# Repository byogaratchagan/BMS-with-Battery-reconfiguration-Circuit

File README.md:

# 2ND Prototype design requiremetns

* Switch circuit
* Switch circuit MOSFET driver and control circuit
    * Planar Transformer design for Gate source Voltage source
* Controller and Display
* Enclosure Design

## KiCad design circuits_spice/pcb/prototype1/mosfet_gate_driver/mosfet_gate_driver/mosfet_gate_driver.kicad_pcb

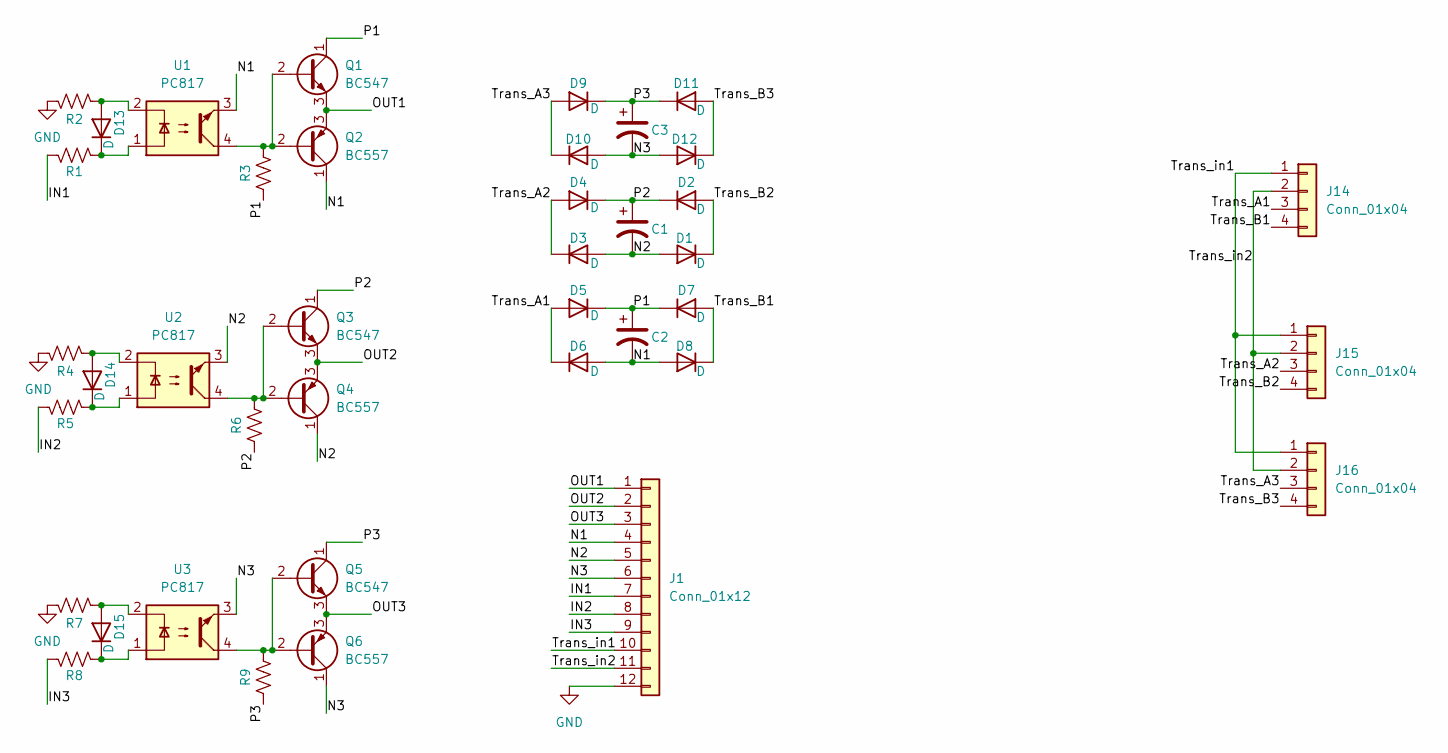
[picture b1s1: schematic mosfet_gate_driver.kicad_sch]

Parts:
C1, C2, C3: C_Polarized_US; CP_Radial_D6.3mm_P2.50mm
D1, D2, D3, D4, D5, D6, D7, D8, D9, D10, D11, D12, D13, D14, D15: D; D_A-405_P7.62mm_Horizontal
J1: Conn_01x12; PinHeader_1x12_P2.54mm_Vertical
J14, J15, J16: Conn_01x04; PinHeader_1x04_P2.54mm_Vertical
Q1, Q3, Q5: BC547; TO-92_Inline
Q2, Q4, Q6: BC557; TO-92_Inline
R1, R2, R3, R4, R5, R6, R7, R8, R9: R_US; R_Axial_DIN0204_L3.6mm_D1.6mm_P1.90mm_Vertical
U1, U2, U3: PC817; DIP-4_W7.62mm

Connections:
/IN1: J1.7, R1.1
/IN2: J1.8, R5.1
/IN3: J1.9, R8.1
/N1: C2.2, D6.2 (A), D8.2 (A), J1.4, Q2.1 (C), U1.3
/N2: C1.2, D1.2 (A), D3.2 (A), J1.5, Q4.1 (C), U2.3
/N3: C3.2, D10.2 (A), D12.2 (A), J1.6, Q6.1 (C), U3.3
/OUT1: J1.1, Q1.3 (E), Q2.3 (E)
/OUT2: J1.2, Q3.3 (E), Q4.3 (E)
/OUT3: J1.3, Q5.3 (E), Q6.3 (E)
/P1: C2.1, D5.1 (K), D7.1 (K), Q1.1 (C), R3.1
/P2: C1.1, D2.1 (K), D4.1 (K), Q3.1 (C), R6.1
/P3: C3.1, D9.1 (K), D11.1 (K), Q5.1 (C), R9.1
/Trans_A1: D5.2 (A), D6.1 (K), J14.3
/Trans_A2: D3.1 (K), D4.2 (A), J15.3
/Trans_A3: D9.2 (A), D10.1 (K), J16.3
/Trans_B1: D7.2 (A), D8.1 (K), J14.4
/Trans_B2: D1.1 (K), D2.2 (A), J15.4
/Trans_B3: D11.2 (A), D12.1 (K), J16.4
/Trans_in1: J1.10, J14.1, J15.1, J16.1
/Trans_in2: J1.11, J14.2, J15.2, J16.2
GND: J1.12, R2.1, R4.1, R7.1
unnamed: D13.2 (A), R2.2, U1.2
unnamed: D13.1 (K), R1.2, U1.1
unnamed: D14.2 (A), R4.2, U2.2
unnamed: D14.1 (K), R5.2, U2.1
unnamed: D15.2 (A), R7.2, U3.2
unnamed: D15.1 (K), R8.2, U3.1
unnamed: Q1.2 (B), Q2.2 (B), R3.2, U1.4
unnamed: Q3.2 (B), Q4.2 (B), R6.2, U2.4
unnamed: Q5.2 (B), Q6.2 (B), R9.2, U3.4

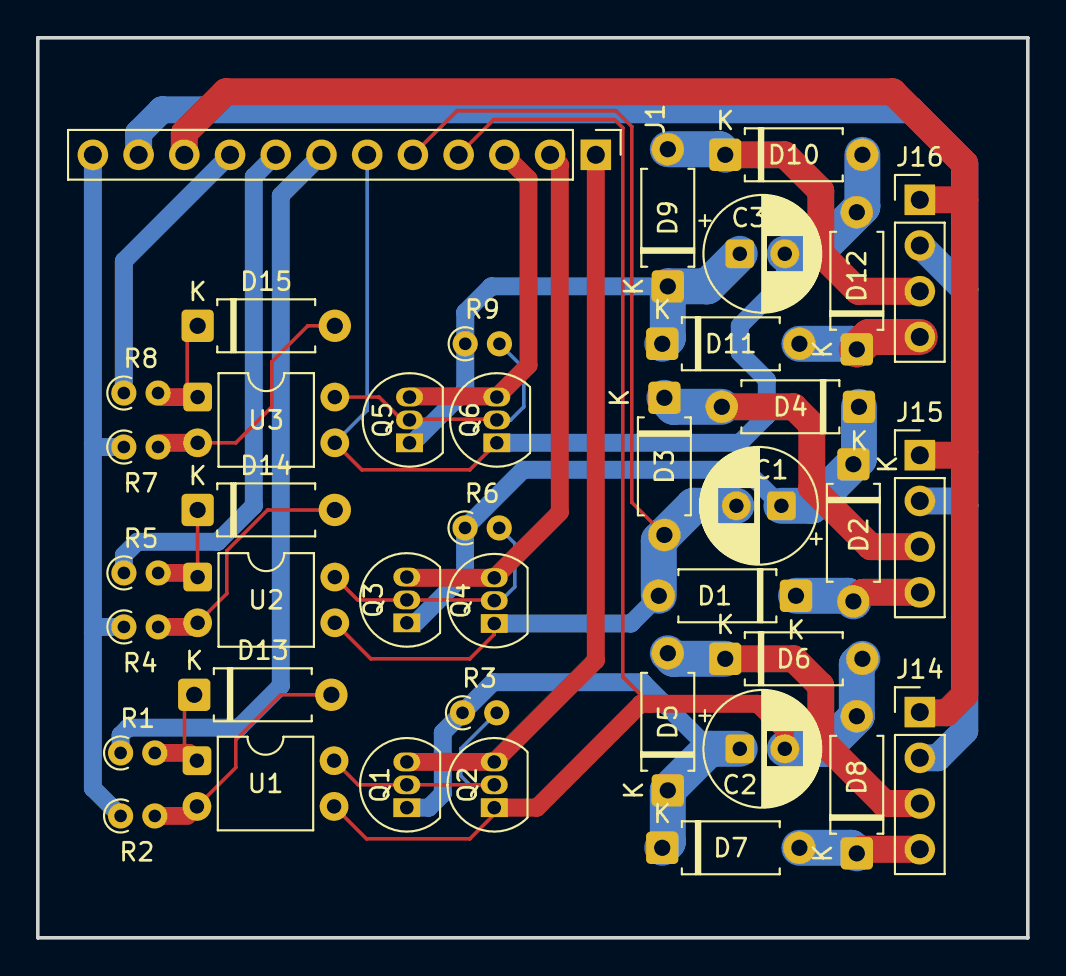
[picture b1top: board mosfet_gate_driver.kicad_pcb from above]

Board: 2 copper layers, 55.0 x 50.0 mm, 40 parts (0 on the bottom side), 30 nets.

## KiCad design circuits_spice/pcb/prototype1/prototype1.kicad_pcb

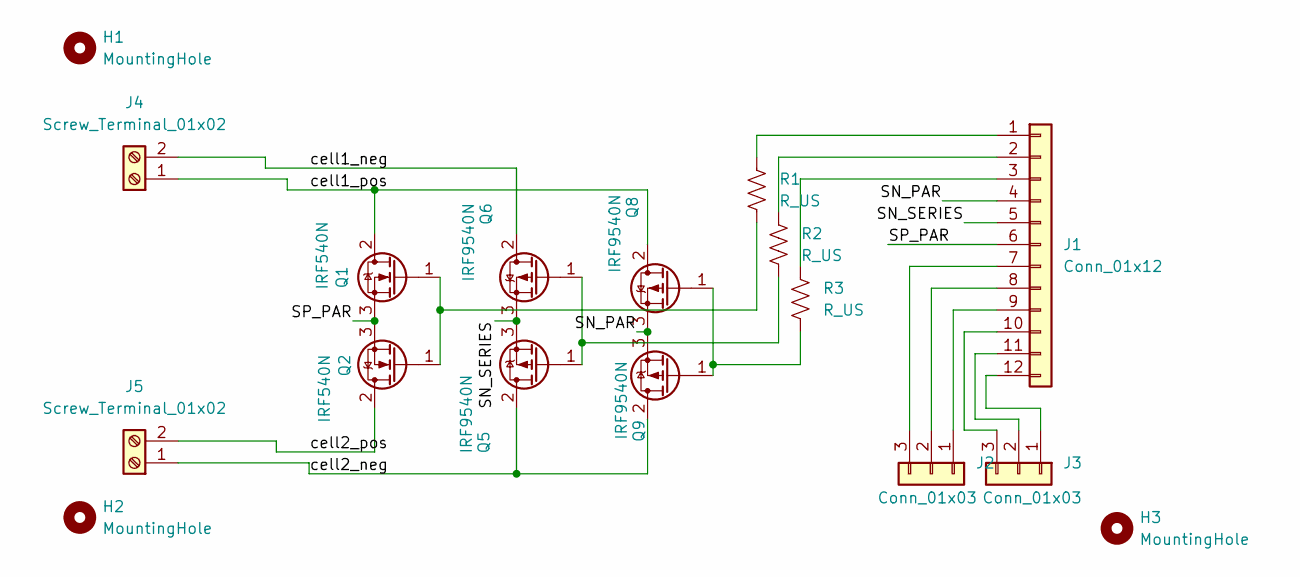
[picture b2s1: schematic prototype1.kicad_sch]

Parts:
H1, H2, H3: MountingHole; MountingHole_3.2mm_M3_Pad_Via
J1: Conn_01x12; PinHeader_1x12_P2.54mm_Vertical
J2, J3: Conn_01x03; PinHeader_1x03_P2.54mm_Vertical
J4, J5: Screw_Terminal_01x02; TerminalBlock_MetzConnect_360291_1x01_Horizontal_ScrewM3.0_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
Q1, Q2: IRF540N; TO-220-3_Vertical
Q5, Q6, Q8, Q9: IRF9540N; TO-220-3_Vertical
R1, R2, R3: R_US; R_Axial_DIN0204_L3.6mm_D1.6mm_P1.90mm_Vertical

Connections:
/SN_PAR: J1.4, Q8.3 (S), Q9.3 (S)
/SN_SERIES: J1.5, Q5.3 (S), Q6.3 (S)
/SP_PAR: J1.6, Q1.3 (S), Q2.3 (S)
/cell1_neg: J4.2, Q6.2 (D)
/cell1_pos: J4.1, Q1.2 (D), Q8.2 (D)
/cell2_neg: J5.1, Q5.2 (D), Q9.2 (D)
/cell2_pos: J5.2, Q2.2 (D)
unnamed: J1.1, R1.1
unnamed: J1.2, R2.1
unnamed: J1.3, R3.1
unnamed: J1.7, J2.3
unnamed: J1.8, J2.2
unnamed: J1.9, J2.1
unnamed: J1.10, J3.3
unnamed: J1.11, J3.2
unnamed: J1.12, J3.1
unnamed: Q1.1 (G), Q2.1 (G), R1.2
unnamed: Q5.1 (G), Q6.1 (G), R2.2
unnamed: Q8.1 (G), Q9.1 (G), R3.2

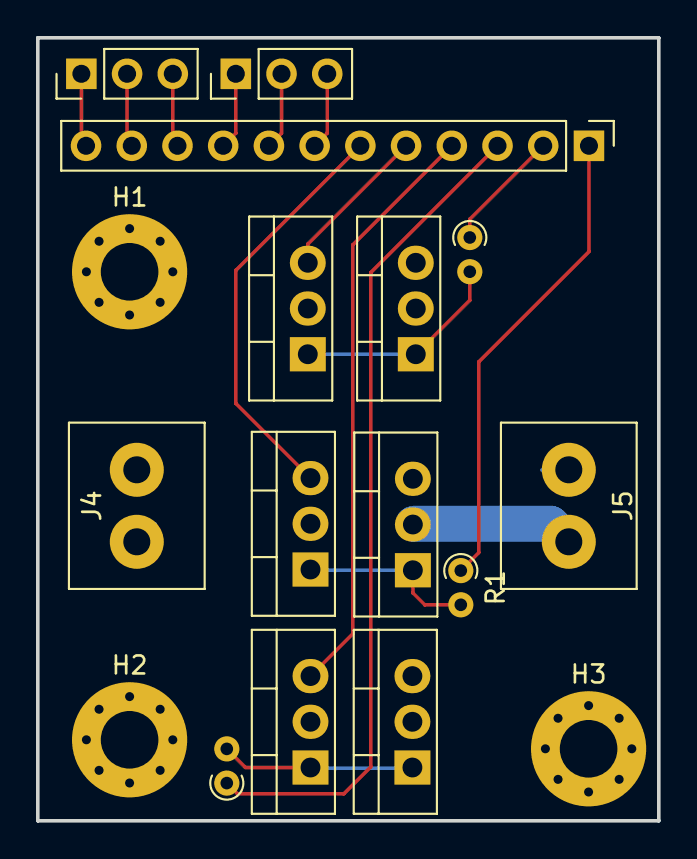
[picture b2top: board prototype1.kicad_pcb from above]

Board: 2 copper layers, 34.5 x 43.5 mm, 17 parts (0 on the bottom side), 19 nets.
